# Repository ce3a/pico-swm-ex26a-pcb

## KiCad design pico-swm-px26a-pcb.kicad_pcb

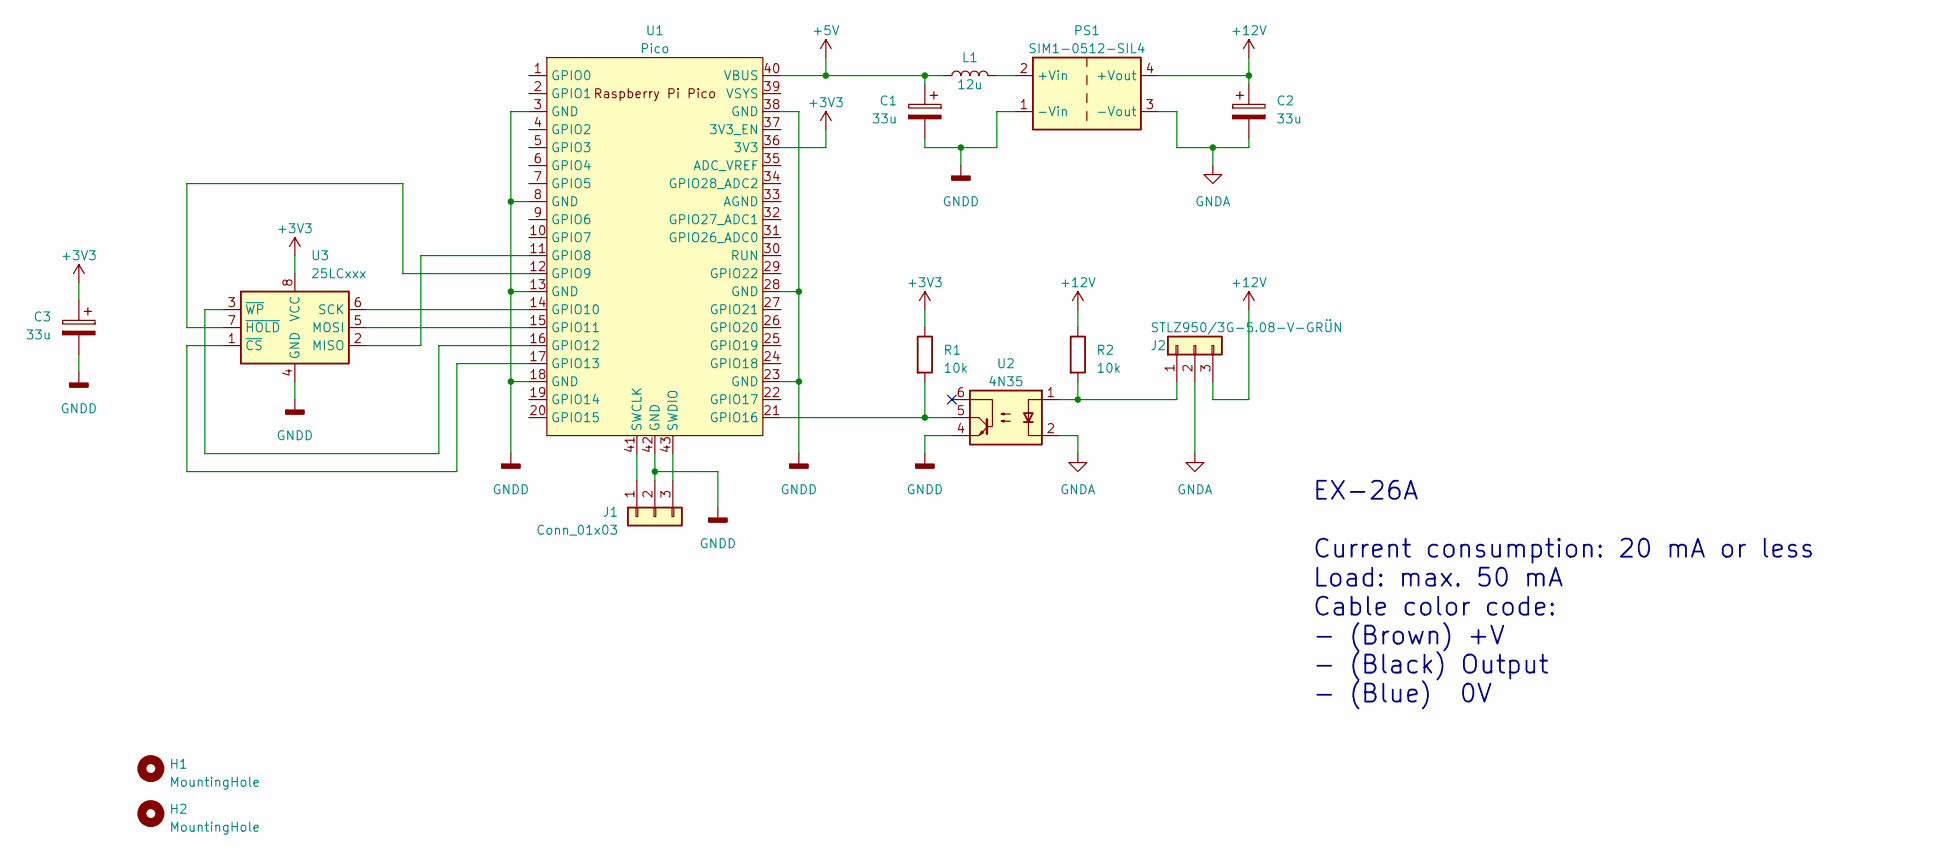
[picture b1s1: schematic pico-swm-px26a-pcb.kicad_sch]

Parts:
C1, C2, C3: 33u; CP_Radial_D5.0mm_P2.00mm
H1, H2: MountingHole; MountingHole_3.2mm_M3
J1: Conn_01x03; PinHeader_1x03_P2.54mm_Vertical
J2: STLZ950/3G-5.08-V-GRÜN; PhoenixContact_MSTBVA_2,5_3-G-5,08_1x03_P5.08mm_Vertical; MPN 50950035121F
L1: 12u; L_Axial_L11.0mm_D4.5mm_P15.24mm_Horizontal_Fastron_MECC; MPN LGA0410-12
PS1: SIM1-0512-SIL4; Converter_DCDC_Murata_MEE1SxxxxSC_THT
R1, R2: 10k; R_Axial_DIN0207_L6.3mm_D2.5mm_P10.16mm_Horizontal
U1: Pico; RPi_Pico_SMD_TH
U2: 4N35; DIP-6_W7.62mm
U3: 25LCxxx; DIP-8_W7.62mm

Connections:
+3V3: C3.1, R1.1, U1.36 (3V3), U3.8 (VCC)
+5V: C1.1, L1.1, U1.40 (VBUS)
+12V: C2.1, J2.3, PS1.4 (+Vout), R2.1
GNDA: C2.2, J2.2, PS1.3 (-Vout), U2.2
GNDD: C1.2, C3.2, J1.2, PS1.1 (-Vin), U1.3 (GND), U1.8 (GND), U1.13 (GND), U1.18 (GND), U1.23 (GND), U1.28 (GND), U1.38 (GND), U1.42 (GND), U2.4, U3.4 (GND)
unnamed: J1.1, U1.41 (SWCLK)
unnamed: J1.3, U1.43 (SWDIO)
unnamed: J2.1, R2.2, U2.1
unnamed: L1.2, PS1.2 (+Vin)
unnamed: U1.11 (GPIO8), U3.2 (MISO)
unnamed: U1.12 (GPIO9), U3.7 (~HOLD)
unnamed: U1.14 (GPIO10), U3.6 (SCK)
unnamed: U1.15 (GPIO11), U3.5 (MOSI)
unnamed: U1.16 (GPIO12), U3.3 (~WP)
unnamed: U1.17 (GPIO13), U3.1 (~CS)
unnamed: R1.2, U1.21 (GPIO16), U2.5

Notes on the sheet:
EX-26A Current consumption: 20 mA or less Load: max. 50 mA Cable color code: - (Brown) +V - (Black) Output - (Blue) 0V

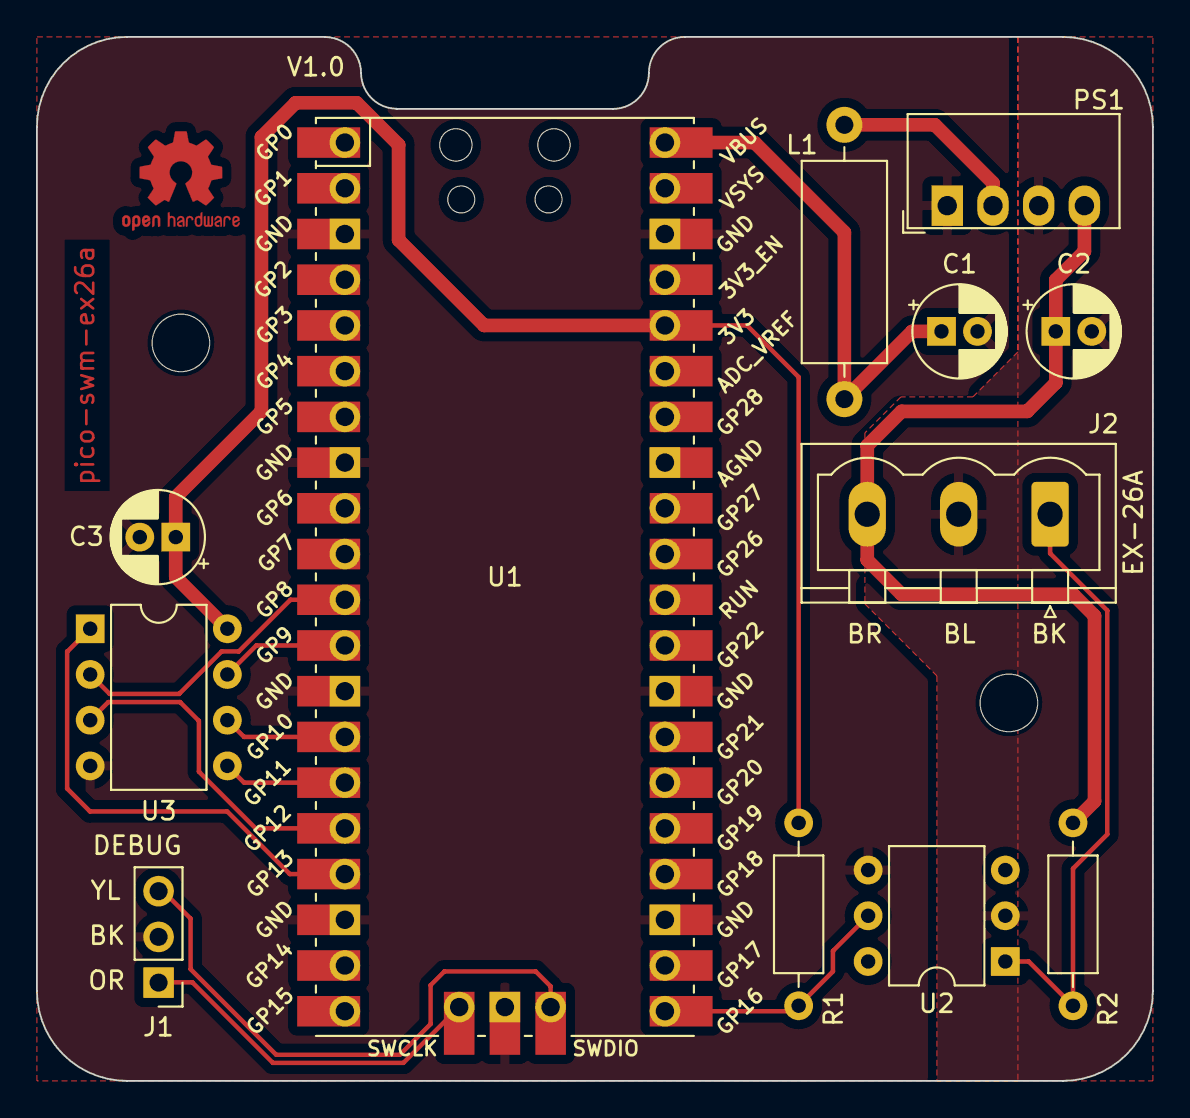
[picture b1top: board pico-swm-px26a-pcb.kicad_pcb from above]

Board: 2 copper layers, 62.0 x 58.0 mm, 14 parts (0 on the bottom side), 16 nets.

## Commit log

2023-12-05 Add EEPROM
2023-12-22 Add EEPROM cap
2023-12-22 Initial routing
2023-12-23 Update BOM
2023-12-23 Ignore .lck files
2023-12-23 Add gerbers (for PCBWay)
